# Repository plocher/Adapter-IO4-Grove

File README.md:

# Adapter-IO4-Grove
## License: CERN Open Hardware Licence v1.2

RJ12/6 breakout board, for Grove style 2mm pitch connector

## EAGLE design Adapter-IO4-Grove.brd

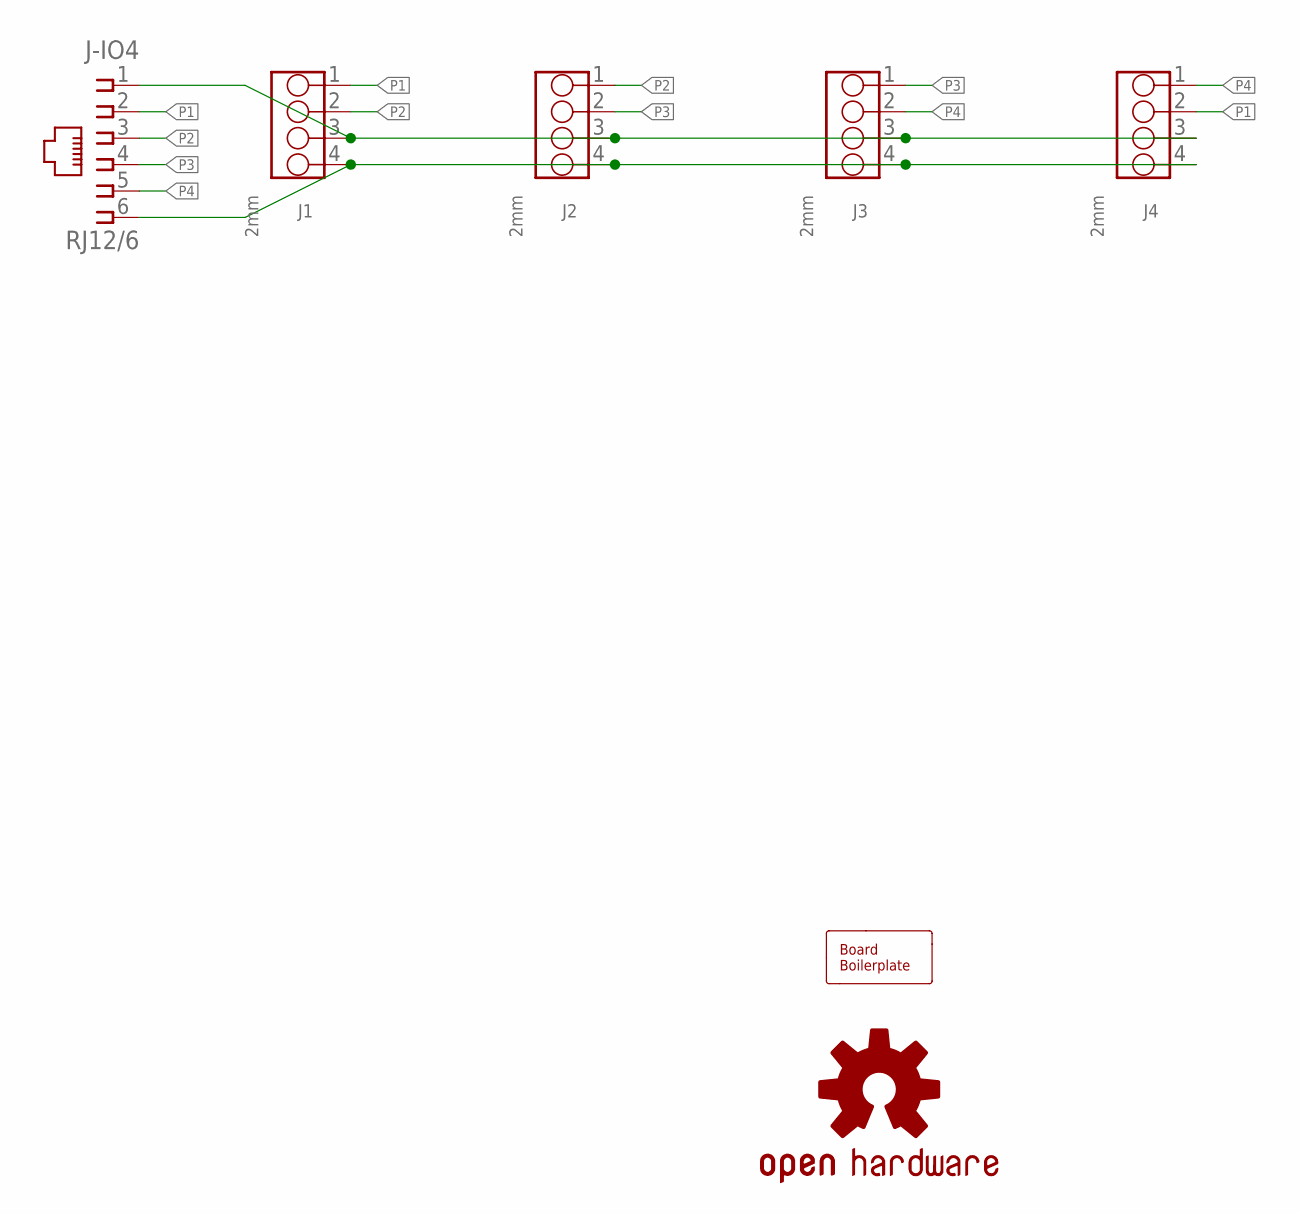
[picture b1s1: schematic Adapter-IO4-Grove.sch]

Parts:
J1, J2, J3, J4: 2mm; 4P-2.0
J-IO4: RJ12/6; RJ25-INVERTED
LOGO1: OSHW; OSHW-LOGO-L
U$1: BOARD; BOARD-SEEED5X5

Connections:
GND: J1.4, J2.4, J3.4, J4.4, J-IO4.6
P1: J1.1, J4.2, J-IO4.2
P2: J1.2, J2.1, J-IO4.3
P3: J2.2, J3.1, J-IO4.4
P4: J3.2, J4.1, J-IO4.5
V5: J1.3, J2.3, J3.3, J4.3, J-IO4.1

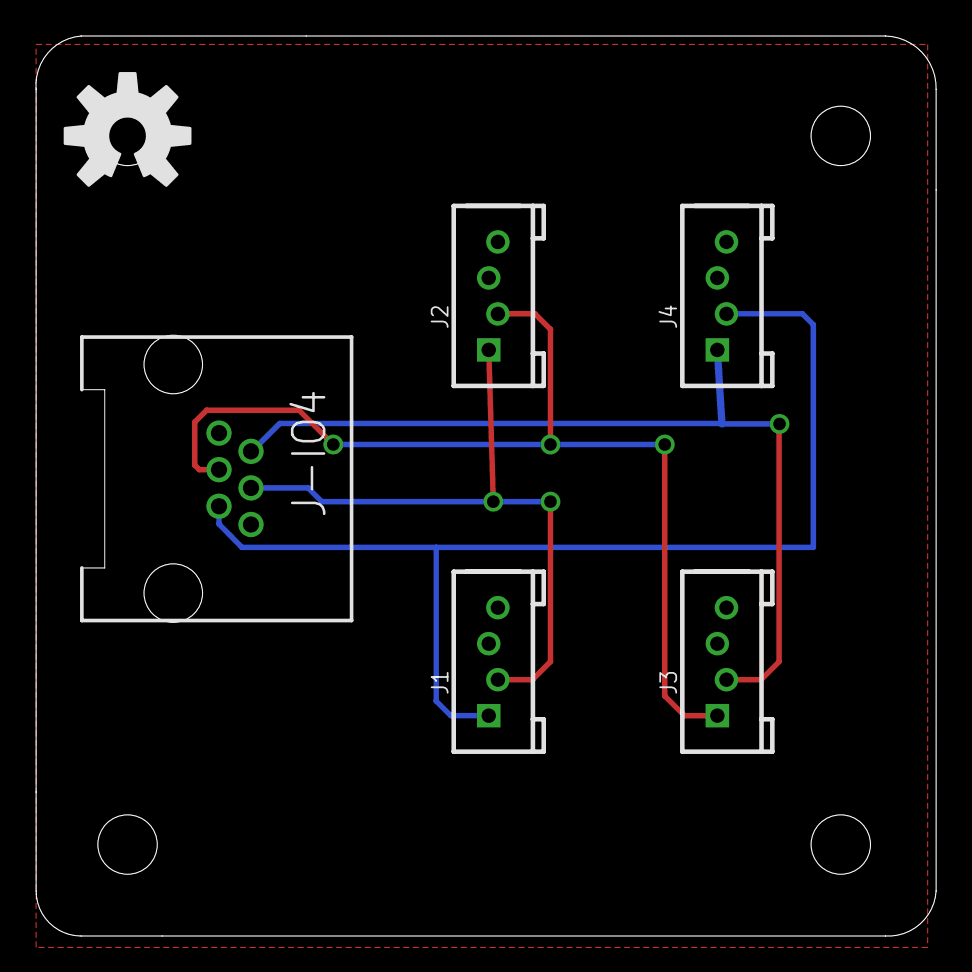
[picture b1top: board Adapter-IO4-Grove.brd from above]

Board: 2 copper layers, 50.0 x 50.0 mm, 7 parts (0 on the bottom side), 6 nets.

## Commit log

2019-12-09 added graphic
2020-05-04 updated tags
2020-10-05 added values for connectors
2020-10-06 normalized values

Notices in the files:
parts and their libraries:
SPCoast: http://freedomdefined.org/OSHW Creative Commons - Attribution - ShareAlike 3.0
